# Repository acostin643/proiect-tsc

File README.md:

# Proiect - Ink Time
**Autor:** Baltag Constantin

## 1. Diagramă Bloc
Diagrama reprezintă arhitectura sistemului InkTime, având în centru microcontrolerul nRF52840.Acesta este conectat prin magistrale dedicate (I2C, SPI, PWM) la senzorii de mișcare, ecranul E-Paper și motorul de vibrații, asigurând o gestionare eficientă a consumului și a interacțiunii.

## 2. Bill Of Materials (BOM)
Mai jos este tabelul cu componentele utilizate, conform specificațiilor proiectului și listei JLC Parts:

| Componentă / Valoare | Cant. | Capsulă | Producător / PN | Sursă (JLC Parts) | Datasheet |
| :--- | :---: | :--- | :--- | :--- | :--- |
| **nRF52840-QIAA** | 1 | aQFN-73 | Nordic | [C115598](https://jlcpcb.com/partdetail/NordicSemicon_nRF52840QIAA/C115598) | [Link](https://infocenter.nordicsemi.com/pdf/nRF52840_PS_v1.1.pdf)  |
| **LSM6DS3TR-C** | 1 | LGA-14L | ST | [C134015](https://jlcpcb.com/partdetail/STMicroelectronics_LSM6DS3TRC/C134015) | [Link](https://www.st.com/resource/en/datasheet/lsm6ds3.pdf)  |
| **Waveshare 1.54inch E-Paper Module** | 1 | FPC-24P | Waveshare | [C2904555](https://jlcpcb.com/partdetail/Waveshare_154inchE_PaperModule/C2904555) | [Link](https://www.waveshare.com/wiki/1.54inch_e-Paper_Module)  |
| **Fit0774** | 1 | SMD | DFRobot | [C3016423](https://jlcpcb.com/partdetail/Fit0774/C3016423) | [Link](https://wiki.dfrobot.com/Micro_Vibration_Motor_3_7V_SKU_FIT0774)  |
| **KH-TYPE-C-16P** | 1 | SMD | Kinghelm | [C710729](https://jlcpcb.com/partdetail/Kinghelm_KHTYPEC16P/C710729) | [Link](https://datasheet.lcsc.com/lcsc/2108132230_Kinghelm-KH-TYPE-C-16P_C710729.pdf)  |

## 3. Descriere Hardware și Funcționalitate
InkTime este un smartwatch proiectat pentru a fi ieftin și open-source, optimizat pentru consum minim de energie.

* **Microcontroler:** SoC nRF52840 gestionează procesarea și comunicarea radio (Bluetooth 5.0).
* **Senzori:** IMU LSM6DS3TR-C este utilizat pentru detecția mișcării, comunicând prin interfața **I2C**.
* **Display:** Ecranul E-Paper oferă o citire excelentă și consum minim, fiind conectat prin **SPI**.
* **Feedback:** Motorul de vibrații (shaker) oferă notificări haptice controlate prin semnal **PWM**.
* **Alimentare:** Include un circuit de încărcare pentru bateria LiPo, mufa USB-C fiind utilizată pentru alimentare și debug.

## 4. Configurație Pini (nRF52840)
Alocarea pinilor a fost realizată pentru a respecta cerințele de design și rutare:

| Pin | Funcție | Destinație | Motivație |
| :--- | :--- | :--- | :--- |
| **P0.17** | CS | Display SPI | Selecția cipului pentru comunicația SPI. |
| **P0.19** | CLK | Display SPI | Semnal de ceas sincronizat. |
| **P0.26** | SDA | IMU I2C | Transfer serial de date I2C. |
| **P0.27** | SCL | IMU I2C | Semnal de ceas I2C. |
| **P1.01** | PWM | Shaker | Controlul intensității vibrațiilor. |
| **P0.13** | Input | Buton | Detectarea interacțiunii utilizatorului. |

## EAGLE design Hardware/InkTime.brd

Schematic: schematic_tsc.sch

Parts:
ANT1: 2450AT18B100E; 2450AT18B100E_ANTC3216X140N
C1, C2, C17, C18: 12pF; NORDIC_NRF_3_RESC0201_L
C1-EP-DR, C39: 10uF; NORDIC_NRF_3_RESC0402_L
C2-EP-DR, C6, C14, C20, C21, C43: 4.7uF; NORDIC_NRF_3_RESC0402_L
C3, C4: 1pF; NORDIC_NRF_3_RESC0201_L
C5, C7, C8, C12, C19: 100nF; NORDIC_NRF_3_RESC0201_L
C9: 820pF; NORDIC_NRF_3_RESC0201_L
C10, C13, C22: N.C.; NORDIC_NRF_3_RESC0201_L
C11: 100pF; NORDIC_NRF_3_RESC0201_L
C15: 1.0uF; NORDIC_NRF_3_RESC0402_L
C16: 47nF; NORDIC_NRF_3_RESC0201_L
C23, C26, C28: 0.1uF; GRM011R60J152KE01L_2_CAPC0201X13N
C24: 10uF; GRM011R60J152KE01L_2_CAPC0201X13N
C25, C33: NORDIC_NRF_3_CAPACITOR_0402_L; NORDIC_NRF_3_RESC0402_L
C27, C42: 0.1uF; NORDIC_NRF_3_RESC0402_L
C29, C30, C31, C37, C38: 1uF; NORDIC_NRF_3_RESC0402_L
D2, D4, D5: ESP32_C6_LIBRARY_5_MBR0530; ESP32_C6_LIBRARY_5_SOD3716X135N
D3: USBLC6-2SC6Y; ESP32_C6_LIBRARY_3_SOT95P280X145-6N
EPD_C1: 1uF/50v; NORDIC_NRF_3_RESC0402_L
EPD_C2, EPD_C6, EPD_C7, EPD_C8, EPD_C9, EPD_C10, EPD_C11, EPD_C12: 1uF/50V; NORDIC_NRF_3_RESC0402_L
EPD_C5: 0.1uF/50V; NORDIC_NRF_3_RESC0402_L
IC1: BQ25180YBGR; BQ25180YBGR_BGA8C40P2X4_100X155X50
IC2: DRV2605YZFR; DRV2605YZFR_BGA9C50P3X3_144X144X62
IC3: BMA423; BMA423_BMA423
IC9: RT6160AWSC; RT6160AWSC_BGA15C40P3X5_140X230X60
J1: 503480-2400; 503480-2400_5034802400
J2: TC2030-IDC; TC2030-IDC_TC2030IDC
J4: KH-TYPE-C-16P; KH-TYPE-C-16P_KINGHELM_KH-TYPE-C-16P
L1: 3.9nH; NORDIC_NRF_2_RESC0201_L
L2: 10uH; NORDIC_NRF_2_RESC0402_L
L3: 15nH; NORDIC_NRF_2_RESC0201_L
L5: 68uH; ESP32_C6_LIBRARY_2_IND_4828-WE-TPC_WRE
L7: FTC252012SR47MBCA; MLP2016SR47MT0S1_INDC2016X100N
Q1: 20V/4.2A/52mΩ/1.4W; ESP32_C6_LIBRARY_4_ESP32_C6_LIBRARY_4_ESP32_C6_LIBRARY_4_ES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
Q3: SI1308EDL-T1-GE3; ESP32_C6_LIBRARY_6_SOT65P210X110-3N
R1_EP_DR: 0.47; ERA-1AEB3401C_0201
R1_USB, R2, R3: CPF0201D7K68C1_CPF0201D7K68C1; CPF0201D7K68C1_0201
R2_EP_DR: 10K; ERA-1AEB3401C_0201
R2_USB: 5k1; CPF0201D7K68C1_0201
R4: 0; CPF0201D7K68C1_0201
R5, R7, R8, R9: 10K; CPF0201D7K68C1_0201
R17, R18: 3K3; CPF0201D7K68C1_0201
R_PWR_EPD: CPF0201D7K68C1_CPF0201D7K68C1; CPF0201D7K68C1_0201
R_TYPE_SEL: 2.2; ERA-1AEB3401C_0201
SJ1: ESP32_C6_LIBRARY_7_JUMPER_SJ
SW_DN: 2025-10-22_07-23-44_LIBRARY_EVP-AKE31ASW_EVP-AKE3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; 2025-10-22_07-23-44_LIBRARY_SW_EVP-AKE31A_PAN
SW_ENT: 2025-10-22_07-23-44_LIBRARY_EVP-AKE31ASW_EVP-AKE3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; 2025-10-22_07-23-44_LIBRARY_SW_EVP-AKE31A_PAN
SW_UP: 2025-10-22_07-23-44_LIBRARY_EVP-AKE31ASW_EVP-AKE3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; 2025-10-22_07-23-44_LIBRARY_SW_EVP-AKE31A_PAN
TP_3.3V, TP_3V3: HECTOR_WATCH_1_TPTP20R; HECTOR_WATCH_1_TP20R
TP_BAT_GND: HECTOR_WATCH_1_TPTP20R; HECTOR_WATCH_1_TP20R
TP_GND: HECTOR_WATCH_1_TPTP20R; HECTOR_WATCH_1_TP20R
TP_ON: HECTOR_WATCH_1_TPTP20R; HECTOR_WATCH_1_TP20R
TP_OP: HECTOR_WATCH_1_TPTP20R; HECTOR_WATCH_1_TP20R
TP_RESET: HECTOR_WATCH_1_TPTP20R; HECTOR_WATCH_1_TP20R
TP_SCL: HECTOR_WATCH_1_TPTP20R; HECTOR_WATCH_1_TP20R
TP_SDA: HECTOR_WATCH_1_TPTP20R; HECTOR_WATCH_1_TP20R
TP_SWDCLK: HECTOR_WATCH_1_TPTP20R; HECTOR_WATCH_1_TP20R
TP_SWDIO: HECTOR_WATCH_1_TPTP20R; HECTOR_WATCH_1_TP20R
TP_SWO: HECTOR_WATCH_1_TPTP20R; HECTOR_WATCH_1_TP20R
TP_VBAT: HECTOR_WATCH_1_TPTP20R; HECTOR_WATCH_1_TP20R
TP_VREG: HECTOR_WATCH_1_TPTP20R; HECTOR_WATCH_1_TP20R
U1: NRF52840_QF; NORDIC_NRF_4_AQFN50P700X700X85_HS-74N
U3: MAX17048G+T10; ESP32_C6_LIBRARY_SON50P200X200X80-9N
X1: 32MHz; NORDIC_NRF_BT-XTAL_2016_N
X2: 32.768kHz; NORDIC_NRF_1_XTAL_3215_N

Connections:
3V3: C6.1, C7.1, C8.1, C12.1, C14.1, C19.1, C25.1, C26.2, C33.1, IC2.C2 (VDD), IC3.3 (VDDIO), IC3.7 (VDD), IC3.10 (CSB), IC9.E2 (VOUT_1), IC9.E3 (VOUT_2), J2.1, Q1.2 (S), R5.2, R7.2, R8.2, R17.1, R18.1, R_PWR_EPD.2, TP_3.3V.TP, TP_3V3.TP, U1.P$A22 (VDD), U1.P$AD14 (VDD), U1.P$AD23 (VDD), U1.P$B1 (VDD), U1.P$W1 (VDD), U1.P$Y2 (VDDH)
ALERT: U1.P$J24 (P0.10/NFC2), U3.5 (!ALERT)
D+: D3.4 (I/O2_2), U1.P$AD6 (D+)
D-: D3.6 (I/O1_2), U1.P$AD4 (D-)
DEC1@C1: C5.1, U1.P$C1 (DEC1)
DEC3@D23: C11.1, U1.P$D23 (DEC3)
DEC3V3@AC5: C20.1, U1.P$AC5 (DEC3V3)
DEC5@N24: C9.1, U1.P$N24 (DEC5)
DN: D3.1 (I/O1_1), J4.A7 (DN1), J4.B7 (DN2)
DP: D3.3 (I/O2_1), J4.A6 (DP1), J4.B6 (DP2)
EPD_3V3: C1-EP-DR.1, EPD_C5.2, J1.15, J1.16, L5.2, Q1.3 (D)
EPD_BUSY: J1.9, U1.P$AD12 (P0.17)
EPD_CS: J1.12, U1.P$K2 (P0.05/AIN3)
EPD_DC: J1.11, U1.P$AD10 (P0.15)
EPD_RST: J1.10, U1.P$AC11 (P0.16)
GDR: J1.2, Q3.1 (G), R2_EP_DR.2
GND: C1.2, C1-EP-DR.2, C2.2, C3.1, C4.1, C5.2, C6.2, C7.2, C8.2, C9.2, C10.2, C11.2, C12.2, C13.2, C14.2, C15.2, C16.2, C17.1, C18.1, C19.2, C20.2, C21.2, C22.1, C23.2, C24.1, C25.2, C26.1, C27.2, C28.1, C29.2, C30.2, C31.2, C33.2, C37.2, C38.2, C39.2, C42.2, C43.2, D3.2 (GND), D4.1 (K), EPD_C1.1, EPD_C2.1, EPD_C5.1, EPD_C6.1, EPD_C7.1, EPD_C8.1, EPD_C9.1, EPD_C10.1, EPD_C11.1, EPD_C12.1, IC1.D2 (GND), IC2.B1 (IN/TRIG), IC2.B3 (GND), IC3.8 (GNDIO), IC3.9 (GND), IC9.B1 (VSEL), IC9.C1 (AGND), IC9.C2 (PGND_1), IC9.C3 (PGND_2), J1.8, J1.17, J1.MP1, J1.MP2, J2.3, J2.5, J4.A1_B12 (GND), J4.A12_B1 (GND), J4.SH1 (SHIELD), J4.SH2 (SHIELD), J4.SH3 (SHIELD), J4.SH4 (SHIELD), R1_USB.1, R2_EP_DR.1, R2_USB.2, R3.1, R9.1, R_TYPE_SEL.1, SJ1.1, SW_DN.1, SW_ENT.1, SW_UP.1, TP_BAT_GND.TP, TP_GND.TP, U1.P$74 (VSS_PAD), U1.P$75 (VSS_PAD), U1.P$76 (VSS_PAD), U1.P$77 (VSS_PAD), U1.P$78 (VSS_PAD), U1.P$79 (VSS_PAD), U1.P$80 (VSS_PAD), U1.P$81 (VSS_PAD), U1.P$82 (VSS_PAD), U1.P$83 (VSS_PAD), U1.P$84 (VSS_PAD), U1.P$85 (VSS_PAD), U1.P$86 (VSS_PAD), U1.P$87 (VSS_PAD), U1.P$88 (VSS_PAD), U1.P$89 (VSS_PAD), U1.P$90 (VSS_PAD), U1.P$B7 (VSS), U1.P$F23 (VSS_PA), U3.1 (CTG), U3.4 (GND), U3.6 (QSTRT), U3.9 (EP), X1.2, X1.4
HAPTIC_EN: IC2.A1 (EN), U1.P$U1 (P0.12)
IMU_INT1: IC3.5 (INT1), U1.P$N1 (P0.08)
IMU_INT2: IC3.6 (INT2), U1.P$P2 (P1.08)
LX1: IC9.B2 (SW1_1), IC9.B3 (SW1_2), L7.1
LX2: IC9.D2 (SW2_1), IC9.D3 (SW2_2), L7.2
MOSI: J1.14, U1.P$B13 (P0.03/AIN1)
unnamed: L2.2, L3.1
unnamed: L2.1, U1.P$B3 (DCC)
unnamed: C10.1, C15.1, C16.1, L3.2, U1.P$B5 (DEC4), U1.P$E24 (DEC6)
unnamed: C13.1, U1.P$A18 (DEC2)
unnamed: C3.2, L1.1, U1.P$H23 (ANT)
unnamed: ANT1.1 (FEED), C4.2, C22.2, L1.2
unnamed: IC1.D1 (TS/MR), R9.2
unnamed: IC3.1 (SDO), R3.2
unnamed: R1_EP_DR.1, R_TYPE_SEL.2, SJ1.2
unnamed: C2-EP-DR.1, D2.1 (K), D4.2 (A)
unnamed: C2-EP-DR.2, D5.2 (A), L5.1, Q3.3 (D)
unnamed: EPD_C2.2, J1.4
unnamed: EPD_C1.2, J1.5
unnamed: EPD_C6.2, J1.18
unnamed: EPD_C7.2, J1.19
unnamed: EPD_C9.2, J1.21
unnamed: EPD_C10.2, J1.22
unnamed: EPD_C12.2, J1.24
unnamed: C28.2, IC2.A2 (REG)
unnamed: J4.A5 (CC1), R1_USB.2
unnamed: J4.B5 (CC2), R2_USB.1
OUT+: IC2.A3 (OUT+), TP_OP.TP
OUT-: IC2.C3 (OUT-), TP_ON.TP
P0.00/XL1@D2: C17.2, U1.P$D2 (P0.00/XL1), X2.1
P0.01/XL2@F2: C18.2, U1.P$F2 (P0.01/XL2), X2.2
P0.04: U1.P$J1 (P0.04/AIN2)
P0.09: U1.P$L24 (P0.09/NFC1)
P0.13: C30.1, R5.1, SW_UP.2, U1.P$AD8 (P0.13)
P0.14: C31.1, R8.1, SW_ENT.2, U1.P$AC9 (P0.14)
P0.19: U1.P$AC15 (P0.19)
P0.20: U1.P$AD16 (P0.20)
P0.21: U1.P$AC17 (P0.21)
P0.22: U1.P$AD18 (P0.22)
P0.23: U1.P$AC19 (P0.23)
P0.24: U1.P$AD20 (P0.24)
P0.25: U1.P$AC21 (P0.25)
P0.26: U1.P$G1 (P0.26)
P0.27: U1.P$H2 (P0.27)
P0.28: U1.P$B11 (P0.28/AIN4)
P0.29: U1.P$A10 (P0.29/AIN5)
P0.30: U1.P$B9 (P0.30/AIN6)
P0.31: U1.P$A8 (P0.31/AIN7)
P1.01: Q1.1 (G), R_PWR_EPD.1, U1.P$Y23 (P1.01)
P1.02: C29.1, R7.1, SW_DN.2, U1.P$W24 (P1.02)
P1.03: U1.P$V23 (P1.03)
P1.04: U1.P$U24 (P1.04)
P1.05: U1.P$T23 (P1.05)
P1.06: U1.P$R24 (P1.06)
P1.07: U1.P$P23 (P1.07)
P1.09: U1.P$R1 (P1.09)
P1.10: U1.P$A20 (P1.10)
P1.11: U1.P$B19 (P1.11)
P1.12: U1.P$B17 (P1.12)
P1.13: U1.P$A16 (P1.13)
P1.14: U1.P$B15 (P1.14)
P1.15: U1.P$A14 (P1.15)
PMIC_INT: IC1.A1 (!INT), U1.P$T2 (P0.11)
PREVGH: D5.1 (K), EPD_C8.2, J1.20
PREVGL: D2.2 (A), EPD_C11.2, J1.23
RESE: J1.3, Q3.2 (S), R1_EP_DR.2
RESET: J2.6, TP_RESET.TP, U1.P$AC13 (P0.18/RESET)
SCK: J1.13, U1.P$A12 (P0.02/AIN0)
SCL: IC1.B1 (SCL), IC2.C1 (SCL), IC3.12 (SCX), IC9.D1 (SCL), R4.2, R17.2, TP_SCL.TP, U1.P$M2 (P0.07), U3.7 (SCL)
SDA: IC1.C1 (SDA), IC2.B2 (SDA), IC3.2 (SDX), IC9.E1 (SDA), R2.2, R18.2, TP_SDA.TP, U1.P$L1 (P0.06), U3.8 (SDA)
SWDCLK: J2.4, TP_SWDCLK.TP, U1.P$AA24 (SWDCLK)
SWDIO: J2.2, TP_SWDIO.TP, U1.P$AC24 (SWDIO)
SWO: TP_SWO.TP, U1.P$AD22 (P1.00)
VBAT: C27.1, C37.1, IC1.C2 (BAT), TP_VBAT.TP, U3.2 (CELL), U3.3 (VDD)
VBUS: C21.1, C38.1, C42.1, C43.1, D3.5 (VBUS), IC1.A2 (IN), J4.A4_B9 (VBUS), J4.A9_B4 (VBUS), U1.P$AD2 (VBUS)
VREG: C23.1, C24.2, C39.1, IC1.B2 (SYS), IC9.A1 (EN), IC9.A2 (VIN_1), IC9.A3 (VIN_2), TP_VREG.TP
XC1@B24: C1.1, U1.P$B24 (XC1), X1.1
XC2@A23: C2.1, U1.P$A23 (XC2), X1.3

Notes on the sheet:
LiPo Charger
SWD
DC/DC
IMU
E-Paper Drive Circuit
E-Paper Display Connector
Fuel Gauge
Haptic Driver
Buttons
USB C Connector & ESD Protection

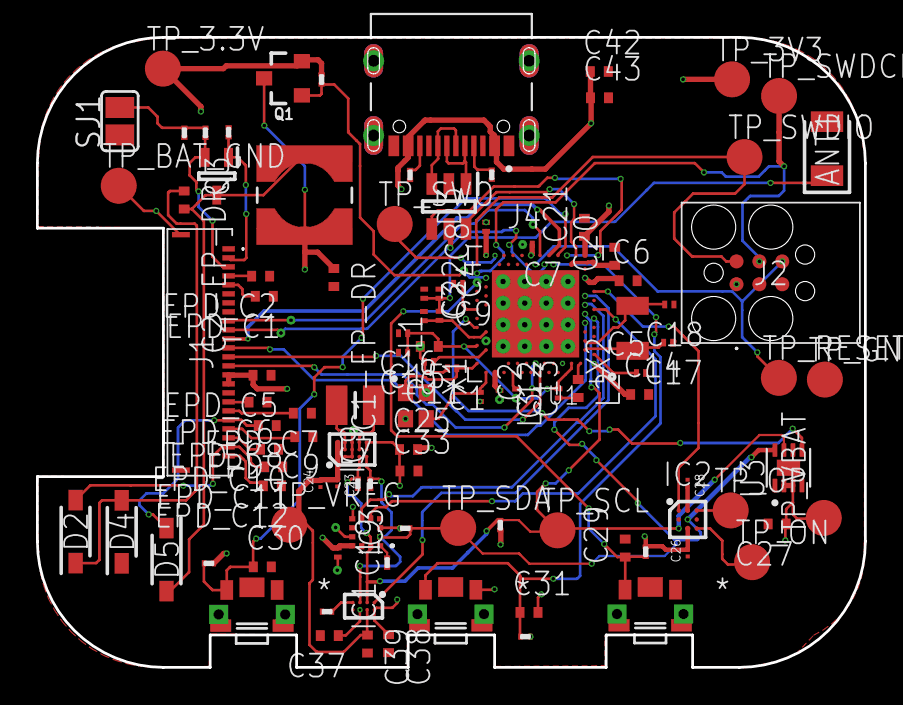
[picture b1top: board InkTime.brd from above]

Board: 4 copper layers, 46.0 x 35.0 mm, 105 parts (0 on the bottom side), 68 nets.

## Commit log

2026-04-10 added folders
2026-04-10 added .gitkeep to track empty folders
2026-04-10 added schematic for inktime
2026-04-10 added pcb
2026-04-21 Expand README with project details and specifications
    Added detailed project information including block diagram, BOM, hardware description, and pin configuration for the Ink Time smartwatch.
2026-04-21 Remove citation markers from README.md
2026-04-21 Revise component table formatting and links
    Updated component table in README with links and formatting.
2026-04-21 Update hardware description in README.md
    Removed citation reference from hardware description.

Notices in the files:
parts and their libraries:
COPYRIGHT: Copyright (C) 2024 Ultra Librarian. All rights reserved.
COPYRIGHT: Copyright (C) 2025 Ultra Librarian. All rights reserved.
